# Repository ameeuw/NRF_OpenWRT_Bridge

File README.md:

# NRF OpenWRT Bridge
Connect an openWRT powererd router to a NRF 2.4 GHz mesh network with this adapter.

Included are files for the printed circuit board (PCB) and software for forwarding messages and sending specific commands.
Additionally a 433 MHz RF-sender and 38 kHz IR-leds can be connected to enable the device to control TV- and stereo-sets and RF controlled outlets.

</img></img>

----------------------------------------

Node broadcasts if button is pressed at boottime:
UUID + 32 Bit Payload

Payload: 

| Bit | Meaning |
|:---:|:--------|
| 1 | Role (0 master/bridge; 1 slave/node) |
| 2-5 | Number of services (0-16) |
| 6  | DMX Passthrough (64 channels, 8 bit per channel) |
| 7  | Infrared (Passthrough (RAW, binary, NEC, SONY, RC5), different devices (Z5500, p2770HD...)) |
| 8  | Radio Frequency 433 MHz (RF-Sockets (passthrough (binary, length etc...))) |
| 9  | Controlled Device (accepts data to handle) |
| 10 | Sensor (emits data) |
| 11 | - |
| 12 | - |
| 13 | - |
| 14 | - |
| 15 | - |
| 16 | - |

| 1 | 2 3 4 5 | 6 | 7 | 8 | 9 | 10 | 11 12 13 14 15 16 |
|:-:|:-------:|:-:|:-:|:-:|:-:|:--:|:-----------------:|
|Role	|	# of Services	|	DMX	|	IR	|	RF	|	Con	|	Sen	|

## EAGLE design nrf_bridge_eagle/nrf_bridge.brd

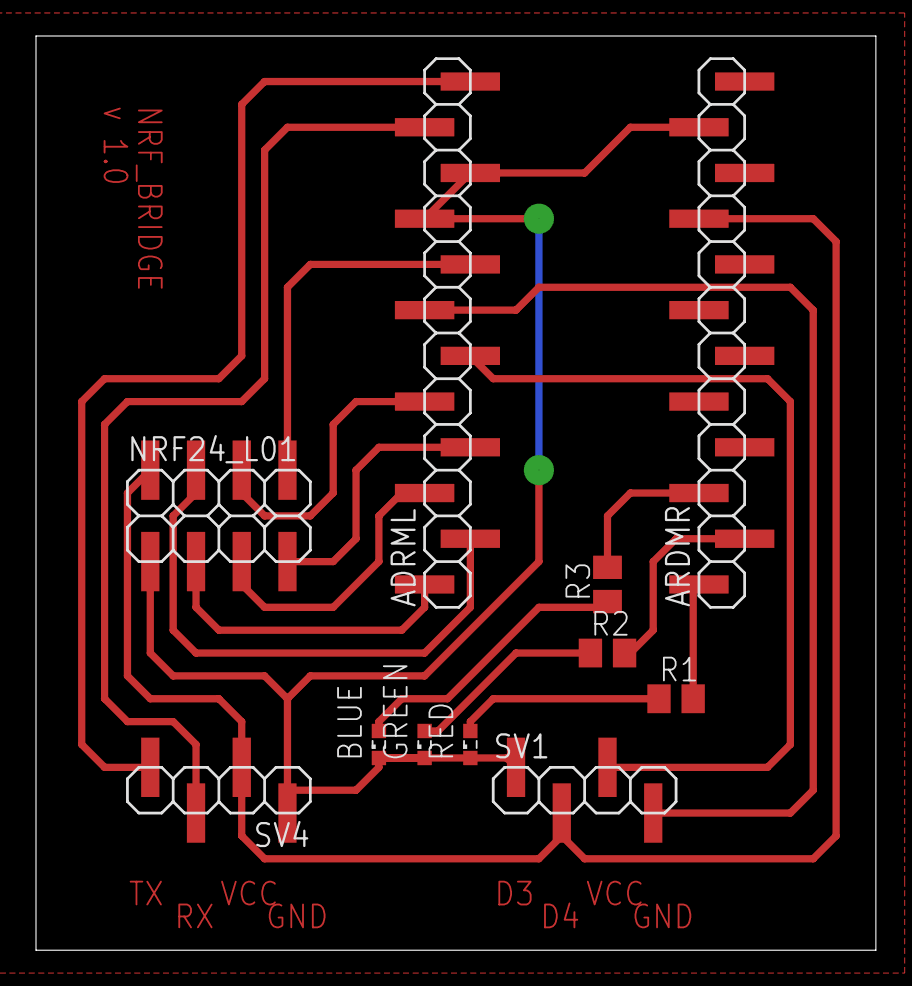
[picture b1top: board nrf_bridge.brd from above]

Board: 2 copper layers, 46.7 x 50.8 mm, 11 parts (0 on the bottom side), 18 nets.

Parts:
ADRML: 1X12SMD
ARDMR: 1X12SMD
BLUE: LED_SML0603
GREEN: LED_SML0603
NRF24_L01: 2X04SMD
R1, R2, R3: M0805
RED: LED_SML0603
SV1, SV4: 1X04SMD

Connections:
CE: ADRML.1, NRF24_L01.3
CSN: ADRML.2, NRF24_L01.4
D3: ADRML.7, SV1.4
D4: ADRML.6, SV1.3
D10: ARDMR.1, R1.2
D14: ARDMR.3, R3.2
D16: ARDMR.2, R2.2
GND: ADRML.9, ADRML.10, ARDMR.11, BLUE.C, GREEN.C, NRF24_L01.1, RED.C, SV1.1, SV4.1
IRQ: ADRML.8, NRF24_L01.8
MISO: ADRML.4, NRF24_L01.7
MOSI: ADRML.5, NRF24_L01.6
unnamed: BLUE.A, R3.1
unnamed: GREEN.A, R2.1
unnamed: R1.1, RED.A
RX: ADRML.11, SV4.3
SCK: ADRML.3, NRF24_L01.5
TX: ADRML.12, SV4.4
VCC: ARDMR.9, NRF24_L01.2, SV1.2, SV4.2

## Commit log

2015-10-14 Restructured folder, edited readme, added picture of pcb, added picture of PCV frame
2015-10-14 Updated readme with table and pictures
2015-10-14 Width of pictures adjusted
2015-10-14 Went back to plain HTML for images and sizing
2015-10-14 Spacing adjusted
